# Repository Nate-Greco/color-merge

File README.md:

# Color Merge Hackpad

## Merge together LED colors

A little game where each key press can merge the colors displayed on the leds. Try to get to the max color without filling up all the leds and running out of moves!

## PCB Overview: 

## Schematic Overview:

## Case Layers:
Bottom:

Top:

Assembled:

## BOM
4 x Cherry MX Switches

16 x SK6812 MINI Leds

1 x XIAO RP2040

4 x Blank DSA Keycaps

7 x M3x16 Bolt

7 x M3 Heatset

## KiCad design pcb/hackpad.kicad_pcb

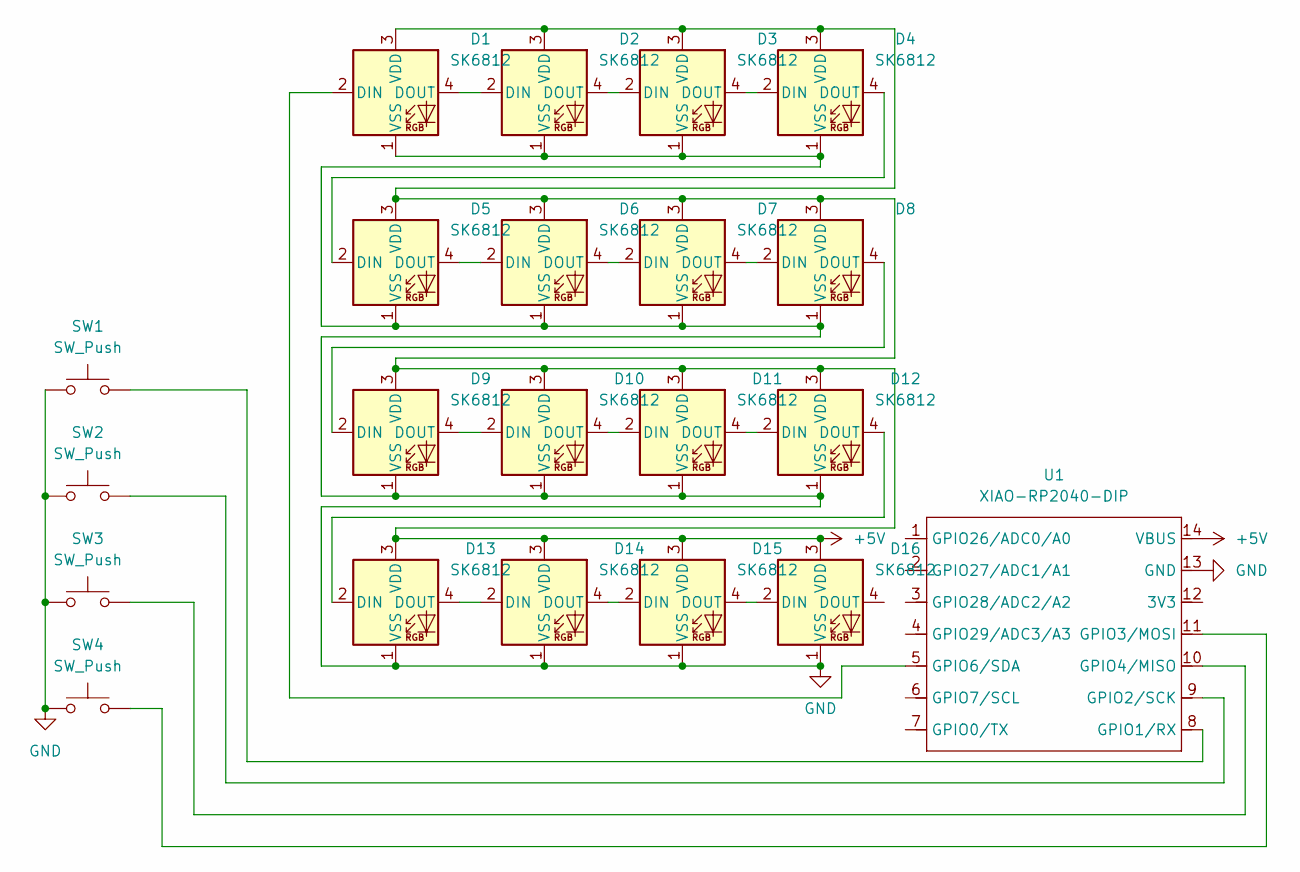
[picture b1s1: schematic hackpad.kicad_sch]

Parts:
D1, D2, D3, D4, D5, D6, D7, D8, D9, D10, D11, D12, D13, D14, D15, D16: SK6812; LED_SK6812MINI_PLCC4_3.5x3.5mm_P1.75mm
SW1, SW2, SW3, SW4: SW_Push; SW_Cherry_MX_1.00u_PCB
U1: XIAO-RP2040-DIP

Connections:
+5V: D1.3 (VDD), D2.3 (VDD), D3.3 (VDD), D4.3 (VDD), D5.3 (VDD), D6.3 (VDD), D7.3 (VDD), D8.3 (VDD), D9.3 (VDD), D10.3 (VDD), D11.3 (VDD), D12.3 (VDD), D13.3 (VDD), D14.3 (VDD), D15.3 (VDD), D16.3 (VDD), U1.14 (VBUS)
GND: D1.1 (VSS), D2.1 (VSS), D3.1 (VSS), D4.1 (VSS), D5.1 (VSS), D6.1 (VSS), D7.1 (VSS), D8.1 (VSS), D9.1 (VSS), D10.1 (VSS), D11.1 (VSS), D12.1 (VSS), D13.1 (VSS), D14.1 (VSS), D15.1 (VSS), D16.1 (VSS), SW1.1, SW2.1, SW3.1, SW4.1, U1.13 (GND)
unnamed: D1.2 (DIN), U1.5 (GPIO6/SDA)
unnamed: D1.4 (DOUT), D2.2 (DIN)
unnamed: D2.4 (DOUT), D3.2 (DIN)
unnamed: D3.4 (DOUT), D4.2 (DIN)
unnamed: D4.4 (DOUT), D5.2 (DIN)
unnamed: D5.4 (DOUT), D6.2 (DIN)
unnamed: D6.4 (DOUT), D7.2 (DIN)
unnamed: D7.4 (DOUT), D8.2 (DIN)
unnamed: D8.4 (DOUT), D9.2 (DIN)
unnamed: D9.4 (DOUT), D10.2 (DIN)
unnamed: D10.4 (DOUT), D11.2 (DIN)
unnamed: D11.4 (DOUT), D12.2 (DIN)
unnamed: D12.4 (DOUT), D13.2 (DIN)
unnamed: D13.4 (DOUT), D14.2 (DIN)
unnamed: D14.4 (DOUT), D15.2 (DIN)
unnamed: D15.4 (DOUT), D16.2 (DIN)
unnamed: SW1.2, U1.8 (GPIO1/RX)
unnamed: SW2.2, U1.9 (GPIO2/SCK)
unnamed: SW4.2, U1.11 (GPIO3/MOSI)
unnamed: SW3.2, U1.10 (GPIO4/MISO)

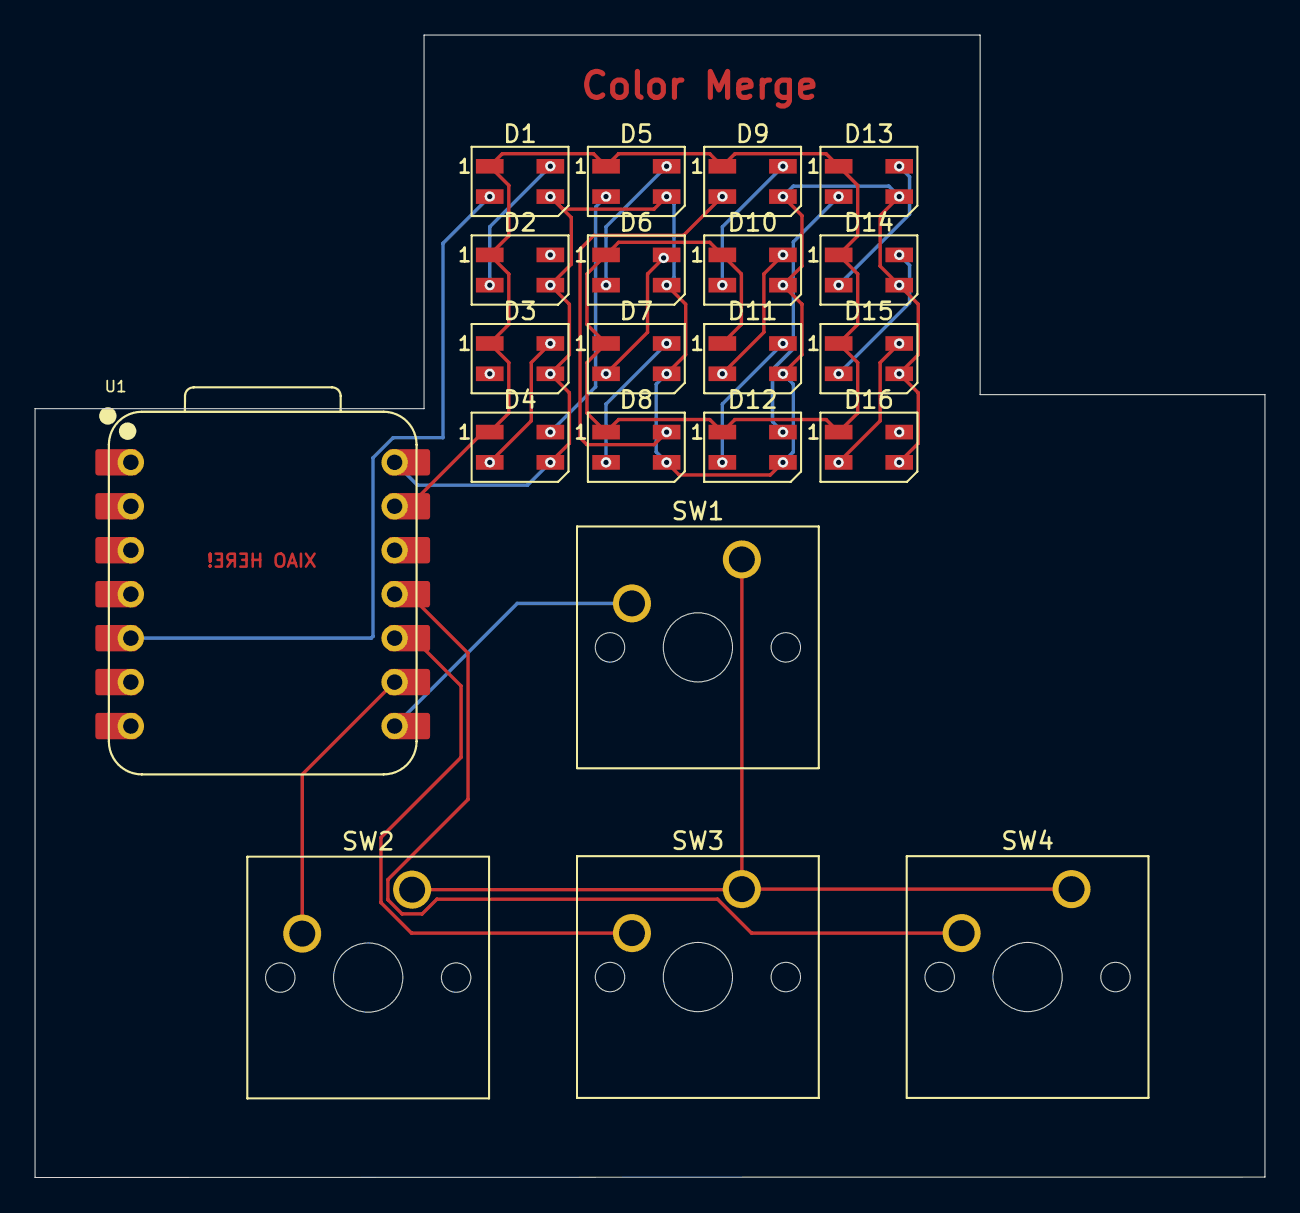
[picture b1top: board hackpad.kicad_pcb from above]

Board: 2 copper layers, 71.1 x 66.0 mm, 21 parts (0 on the bottom side), 22 nets.
